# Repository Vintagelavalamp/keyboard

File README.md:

Simple Keyboard project by Tobias Roest/Vintagelavalamp.
Heavily inspired by the SICK-68 by FIXME.
I wanted something similar, but with a PCB.
PCB footprints are already in KiCad.
Teensy Libraries from https://github.com/XenGi/teensy.pretty

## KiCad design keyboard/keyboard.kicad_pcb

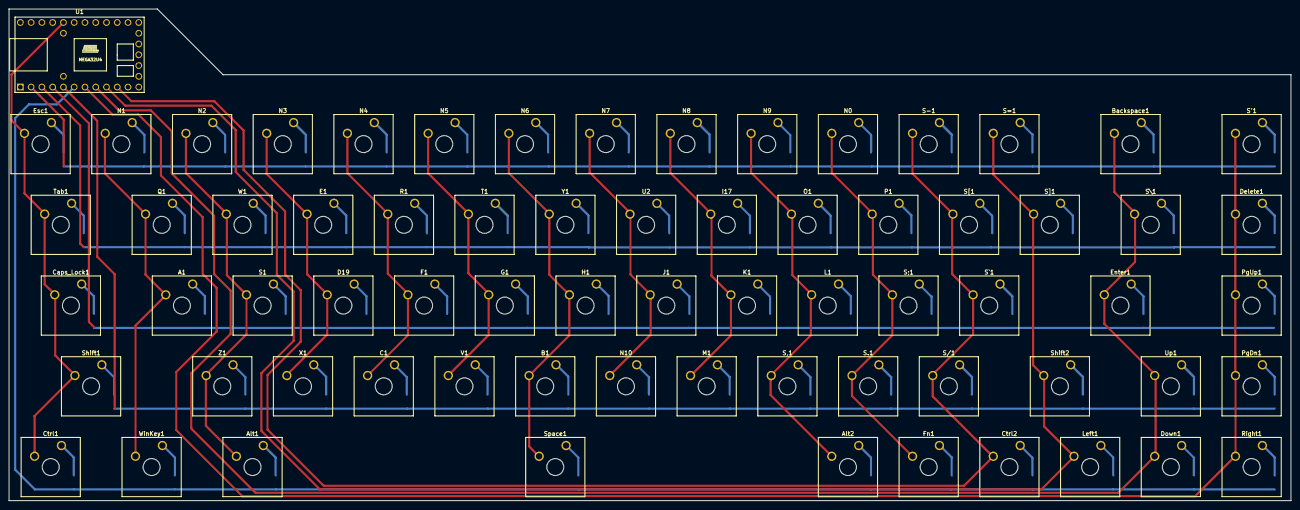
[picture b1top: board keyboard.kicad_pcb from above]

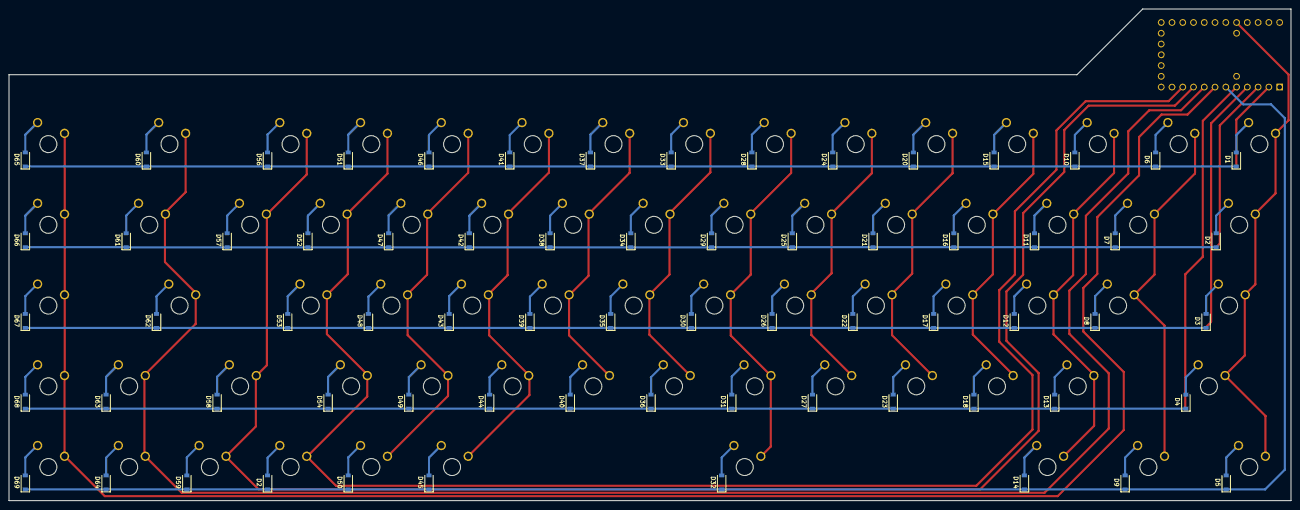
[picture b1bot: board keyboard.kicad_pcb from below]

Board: 2 copper layers, 302.5 x 116.0 mm, 137 parts (68 on the bottom side), 88 nets.

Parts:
A1: SW_SPST; SW_Cherry_MX_1.00u_Plate
Alt1: SW_SPST; SW_Cherry_MX_1.25u_Plate
Alt2: SW_SPST; SW_Cherry_MX_1.00u_Plate
B1: SW_SPST; SW_Cherry_MX_1.00u_Plate
Backspace1: SW_SPST; SW_Cherry_MX_2.00u_Plate
C1: SW_SPST; SW_Cherry_MX_1.00u_Plate
Caps_Lock1: SW_SPST; SW_Cherry_MX_1.75u_Plate
Ctrl1: SW_SPST; SW_Cherry_MX_1.25u_Plate
Ctrl2: SW_SPST; SW_Cherry_MX_1.00u_Plate
D1, D2, D2#2, D3, D4, D5, D6, D7, D8, D9, D10, D11, D12, D13, D14, D15, D16, D17, D18, D20, D21, D22, D23, D24, D25, D26, D27, D28, D29, D30, D31, D32, D33, D34, D35, D36, D37, D38, D39, D40, D41, D42, D43, D44, D45, D46, D47, D48, D49, D50, D51, D52, D53, D54, D56, D57, D58, D59, D60, D61, D62, D63, D64, D65, D66, D67, D68, D69: 1N4148W; D_SOD-123
D19: SW_SPST; SW_Cherry_MX_1.00u_Plate
Delete1: SW_SPST; SW_Cherry_MX_1.00u_Plate
Down1: SW_SPST; SW_Cherry_MX_1.00u_Plate
E1: SW_SPST; SW_Cherry_MX_1.00u_Plate
Enter1: SW_SPST; SW_Cherry_MX_2.25u_Plate
Esc1: SW_SPST; SW_Cherry_MX_1.00u_Plate
F1: SW_SPST; SW_Cherry_MX_1.00u_Plate
Fn1: SW_SPST; SW_Cherry_MX_1.00u_Plate
G1: SW_SPST; SW_Cherry_MX_1.00u_Plate
H1: SW_SPST; SW_Cherry_MX_1.00u_Plate
I17: SW_SPST; SW_Cherry_MX_1.00u_Plate
J1: SW_SPST; SW_Cherry_MX_1.00u_Plate
K1: SW_SPST; SW_Cherry_MX_1.00u_Plate
L1: SW_SPST; SW_Cherry_MX_1.00u_Plate
Left1: SW_SPST; SW_Cherry_MX_1.00u_Plate
M1: SW_SPST; SW_Cherry_MX_1.00u_Plate
N0, N1, N2, N3, N4, N5, N6, N7, N8, N9, N10: SW_SPST; SW_Cherry_MX_1.00u_Plate
O1: SW_SPST; SW_Cherry_MX_1.00u_Plate
P1: SW_SPST; SW_Cherry_MX_1.00u_Plate
PgDn1: SW_SPST; SW_Cherry_MX_1.00u_Plate
PgUp1: SW_SPST; SW_Cherry_MX_1.00u_Plate
Q1: SW_SPST; SW_Cherry_MX_1.00u_Plate
R1: SW_SPST; SW_Cherry_MX_1.00u_Plate
Right1: SW_SPST; SW_Cherry_MX_1.00u_Plate
S1, S.1: SW_SPST; SW_Cherry_MX_1.00u_Plate
S'1: SW_SPST; SW_Cherry_MX_1.00u_Plate
S,1: SW_SPST; SW_Cherry_MX_1.00u_Plate
S-1: SW_SPST; SW_Cherry_MX_1.00u_Plate
S/1: SW_SPST; SW_Cherry_MX_1.00u_Plate
S;1: SW_SPST; SW_Cherry_MX_1.00u_Plate
S=1: SW_SPST; SW_Cherry_MX_1.00u_Plate
S[1: SW_SPST; SW_Cherry_MX_1.00u_Plate
S\1: SW_SPST; SW_Cherry_MX_1.50u_Plate
S]1: SW_SPST; SW_Cherry_MX_1.00u_Plate
S`1: SW_SPST; SW_Cherry_MX_1.00u_Plate
Shift1: SW_SPST; SW_Cherry_MX_2.25u_Plate
Shift2: SW_SPST; SW_Cherry_MX_1.75u_Plate
Space1: SW_SPST; SW_Cherry_MX_6.25u_Plate
T1: SW_SPST; SW_Cherry_MX_1.00u_Plate
Tab1: SW_SPST; SW_Cherry_MX_1.50u_Plate
U1: Teensy2.0_(C); Teensy2.0
U2: SW_SPST; SW_Cherry_MX_1.00u_Plate
Up1: SW_SPST; SW_Cherry_MX_1.00u_Plate
V1: SW_SPST; SW_Cherry_MX_1.00u_Plate
W1: SW_SPST; SW_Cherry_MX_1.00u_Plate
WinKey1: SW_SPST; SW_Cherry_MX_1.25u_Plate
X1: SW_SPST; SW_Cherry_MX_1.00u_Plate
Y1: SW_SPST; SW_Cherry_MX_1.00u_Plate
Z1: SW_SPST; SW_Cherry_MX_1.00u_Plate

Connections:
unnamed: A1.1, D8.2
unnamed: A1.2, N1.2, Q1.2, U1.24, WinKey1.2
unnamed: Alt1.1, D14.2
unnamed: Alt1.2, N2.2, S1.2, U1.23, W1.2, Z1.2
unnamed: Alt2.1, D45.2
unnamed: Alt2.2, L1.2, N9.2, O1.2, S,1.2, U1.12
unnamed: B1.1, D31.2
unnamed: B1.2, H1.2, N6.2, Space1.2, U1.19, Y1.2
unnamed: Backspace1.1, D60.2
unnamed: Backspace1.2, Down1.2, Enter1.2, S\1.2, U1.8, Up1.2
unnamed: C1.1, D23.2
unnamed: C1.2, F1.2, N4.2, R1.2, U1.21
unnamed: Caps_Lock1.1, D3.2
unnamed: Caps_Lock1.2, Ctrl1.2, Esc1.2, Shift1.2, Tab1.2, U1.25
unnamed: Ctrl1.1, D5.2
unnamed: Ctrl2.1, D2.2
unnamed: Ctrl2.2, S-1.2, S/1.2, S[1.2, S`1.2, U1.10
unnamed: D1.1, D6.1, D10.1, D15.1, D20.1, D24.1, D28.1, D33.1, D37.1, D41.1, D46.1, D51.1, D56.1, D60.1, D65.1, U1.2
unnamed: D1.2, Esc1.1
unnamed: D2#2.2, Tab1.1
unnamed: D4.2, Shift1.1
unnamed: D6.2, N1.1
unnamed: D7.2, Q1.1
unnamed: D9.2, WinKey1.1
unnamed: D10.2, N2.1
unnamed: D2#2.1, D7.1, D11.1, D16.1, D21.1, D25.1, D29.1, D34.1, D38.1, D42.1, D47.1, D52.1, D57.1, D61.1, D66.1, U1.3
unnamed: D11.2, W1.1
unnamed: D3.1, D8.1, D12.1, D17.1, D22.1, D26.1, D30.1, D35.1, D39.1, D43.1, D48.1, D53.1, D62.1, D67.1, U1.4
unnamed: D12.2, S1.1
unnamed: D4.1, D13.1, D18.1, D23.1, D27.1, D31.1, D36.1, D40.1, D44.1, D49.1, D54.1, D58.1, D63.1, D68.1, U1.5
unnamed: D13.2, Z1.1
unnamed: D2.1, D5.1, D9.1, D14.1, D32.1, D45.1, D50.1, D59.1, D64.1, D69.1, U1.6
unnamed: D15.2, N3.1
unnamed: D16.2, E1.1
unnamed: D17.2, D19.1
unnamed: D18.2, X1.1
unnamed: D19.2, E1.2, N3.2, U1.22, X1.2
unnamed: D20.2, N4.1
unnamed: D21.2, R1.1
unnamed: D22.2, F1.1
unnamed: D24.2, N5.1
unnamed: D25.2, T1.1
unnamed: D26.2, G1.1
unnamed: D27.2, V1.1
unnamed: D28.2, N6.1
unnamed: D29.2, Y1.1
unnamed: D30.2, H1.1
unnamed: D32.2, Space1.1
unnamed: D33.2, N7.1
unnamed: D34.2, U2.1
unnamed: D35.2, J1.1
unnamed: D36.2, N10.1
unnamed: D37.2, N8.1
unnamed: D38.2, I17.1
unnamed: D39.2, K1.1
unnamed: D40.2, M1.1
unnamed: D41.2, N9.1
unnamed: D42.2, O1.1
unnamed: D43.2, L1.1
unnamed: D44.2, S,1.1
unnamed: D46.2, N0.1
unnamed: D47.2, P1.1
unnamed: D48.2, S;1.1
unnamed: D49.2, S.1.1
unnamed: D50.2, Fn1.1
unnamed: D51.2, S-1.1
unnamed: D52.2, S[1.1
unnamed: D53.2, S`1.1
unnamed: D54.2, S/1.1
unnamed: D56.2, S=1.1
unnamed: D57.2, S]1.1
unnamed: D58.2, Shift2.1
unnamed: D59.2, Left1.1
unnamed: D61.2, S\1.1
unnamed: D62.2, Enter1.1
unnamed: D63.2, Up1.1
unnamed: D64.2, Down1.1
unnamed: D65.2, S'1.1
unnamed: D66.2, Delete1.1
unnamed: D67.2, PgUp1.1
unnamed: D68.2, PgDn1.1
unnamed: D69.2, Right1.1
unnamed: Delete1.2, PgDn1.2, PgUp1.2, Right1.2, S'1.2, U1.7
unnamed: Fn1.2, N0.2, P1.2, S.1.2, S;1.2, U1.11
unnamed: G1.2, N5.2, T1.2, U1.20, V1.2
unnamed: I17.2, K1.2, M1.2, N8.2, U1.13
unnamed: J1.2, N7.2, N10.2, U1.17, U2.2
unnamed: Left1.2, S=1.2, S]1.2, Shift2.2, U1.9

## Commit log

2021-02-14 Made KiCad project
    KiCad project files added
2021-02-14 Finished schematic and started work on PCB
2021-02-14 Worked on PCB Layout
2021-02-15 Continued work on wiring
